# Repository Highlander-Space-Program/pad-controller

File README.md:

# Pad controller PCB

This PCB will be located on our static fire test stand. It will be responsibe for controlling the ignition and fuel systems.

Make sure to clone submodules when cloning this repository.

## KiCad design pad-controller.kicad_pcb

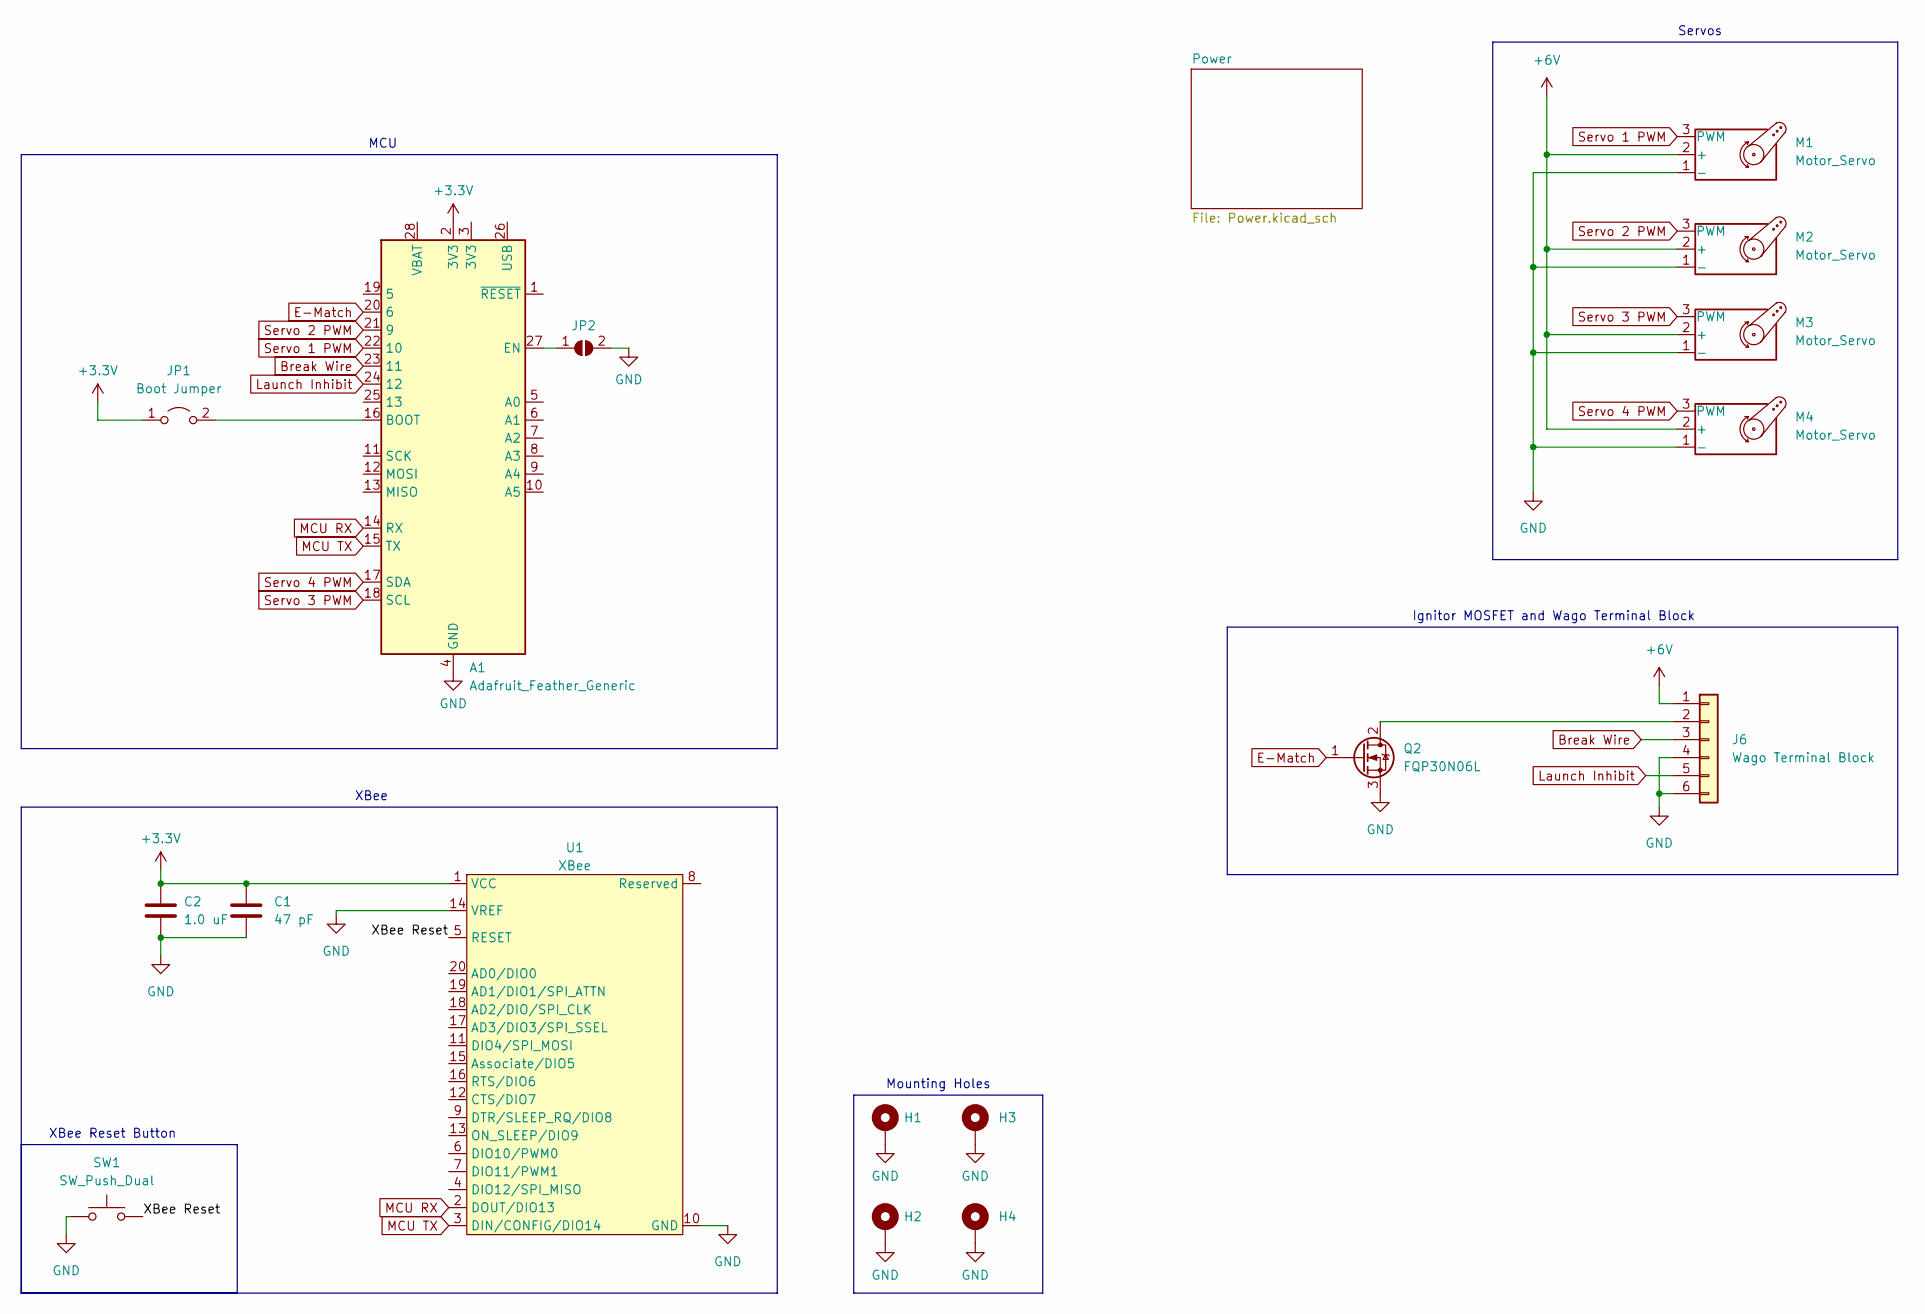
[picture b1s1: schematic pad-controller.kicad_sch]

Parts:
A1: Adafruit_Feather_Generic; Adafruit_Feather
C1: 47 pF; C_0805_2012Metric; Part No. GRM21A5C2D470JW01D
C2: 1.0 uF; C_0805_2012Metric; Part No. GRM219R7YA105MA12D
H1, H2, H3, H4: MountingHole_Pad; MountingHole_4mm_Pad_Via
J6: Wago Terminal Block; WAGO_2601-1106_lever_terminal_block; Part No. 2601-1106
JP1: Boot Jumper; PinHeader_1x02_P2.54mm_Vertical
JP2: SolderJumper-2_P1.3mm_Open_TrianglePad1.0x1.5mm
M1, M2, M3, M4: Motor_Servo; PinHeader_1x03_P2.54mm_Vertical
Q2: FQP30N06L; TO-220-3_Vertical; Part No. FQP30N06L
SW1: SW_Push_Dual; SW_PUSH_6mm
U1: XBee; XBee-PRO 900HP

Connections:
+3.3V: A1.2 (3V3), C1.1, C2.1, JP1.1 (A), U1.1 (VCC); also elsewhere on the board
+6V: J6.1, M1.2 (+), M2.2 (+), M3.2 (+), M4.2 (+); also elsewhere on the board
/XBee Reset: SW1.1, U1.5 (RESET)
Break Wire: A1.23 (11), J6.3
E-Match: A1.20 (6), Q2.1 (G)
GND: A1.4 (GND), C1.2, C2.2, H1.1, H2.1, H3.1, H4.1, J6.4, J6.6, JP2.2 (B), M1.1 (-), M2.1 (-), M3.1 (-), M4.1 (-), Q2.3 (S), SW1.2, U1.10 (GND), U1.14 (VREF); also elsewhere on the board
Launch Inhibit: A1.24 (12), J6.5
MCU RX: A1.14 (RX), U1.2 (DOUT/DIO13)
MCU TX: A1.15 (TX), U1.3 (DIN/CONFIG/DIO14)
unnamed: A1.27 (EN), JP2.1 (A)
unnamed: A1.16 (BOOT), JP1.2 (B)
unnamed: J6.2, Q2.2 (D)
Servo 1 PWM: A1.22 (10), M1.3 (PWM)
Servo 2 PWM: A1.21 (9), M2.3 (PWM)
Servo 3 PWM: A1.18 (SCL), M3.3 (PWM)
Servo 4 PWM: A1.17 (SDA), M4.3 (PWM)

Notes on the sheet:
Servos
Mounting Holes
XBee Reset Button
MCU
XBee
Ignitor MOSFET and Wago Terminal Block

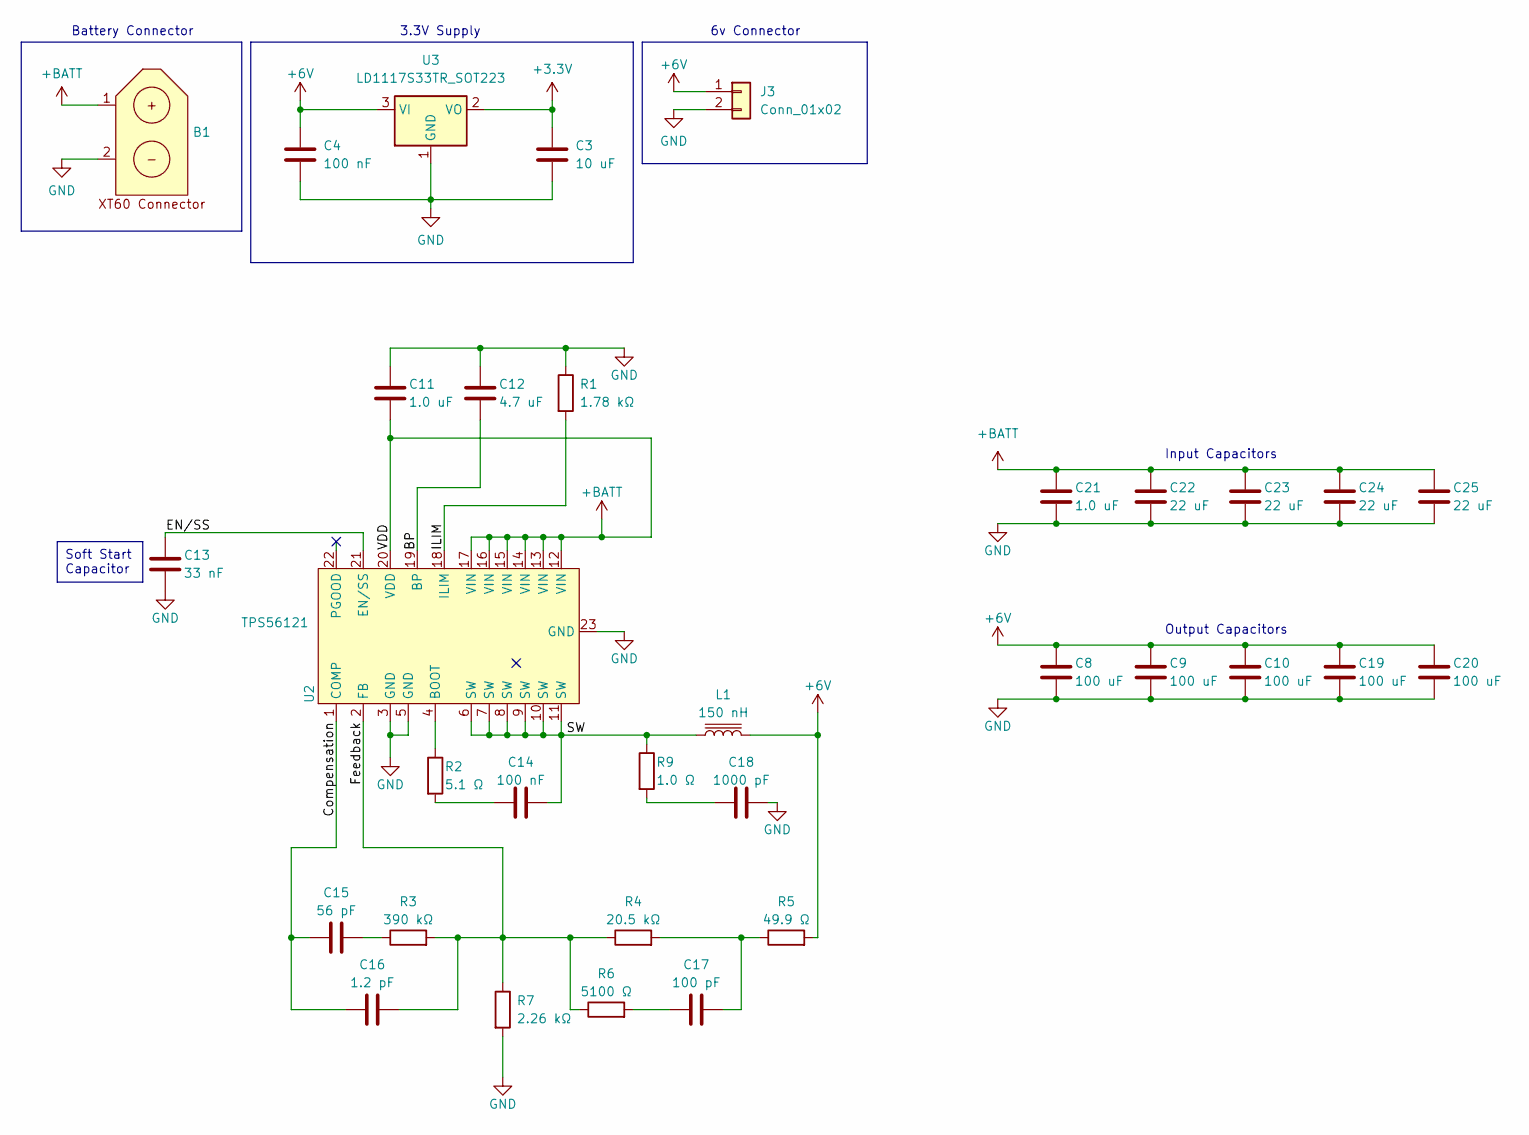
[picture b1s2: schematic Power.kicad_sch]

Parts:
B1: AMASS_XT60-M_1x02_P7.20mm_Vertical
C3: 10 uF; C_0805_2012Metric; Part No. GRM21BR61C106KE15K
C4, C14: 100 nF; C_0805_2012Metric; Part No. GCM21BR72A104KA37L
C8, C9, C10, C19, C20: 100 uF; C_1210_3225Metric; Part No. GRM32EC70J107ME15K
C11, C21: 1.0 uF; C_0805_2012Metric; Part No. GRM219R7YA105MA12D
C12: 4.7 uF; C_0805_2012Metric; Part No. GRM21BR71C475ME51K
C13: 33 nF; C_0805_2012Metric; Part No. GCM219R72A333KA37D
C15: 56 pF; C_0805_2012Metric; Part No. GRM21A5C2E560JW01D
C16: 1.2 pF; C_0805_2012Metric; Part No. CC0805BRNPO9BN1R2
C17: 100 pF; C_0805_2012Metric; Part No. CL21C101JCANNNC
C18: 1000 pF; C_0805_2012Metric; Part No. GRM2165C2A102JA01D
C22, C23, C24, C25: 22 uF; C_1210_3225Metric; Part No. GRM32ER71E226KE15K
J3: Conn_01x02; SolderWire-2sqmm_1x02_P7.8mm_D2mm_OD3.9mm
L1: 150 nH; L_Sumida_CDMC6D28_7.25x6.5mm; Part No. 0624CDMCCDS-R15MC
R1: 1.78 kΩ; R_0805_2012Metric; Part No. RC0805FR-071K78L
R2: 5.1 Ω; R_0805_2012Metric; Part No. RC0805FR-075R1L
R3: 390 kΩ; R_0805_2012Metric; Part No. RC0805FR-07390KL
R4: 20.5 kΩ; R_0805_2012Metric; Part No. RC0805FR-0720K5L
R5: 49.9 Ω; R_0805_2012Metric; Part No. RC0805FR-0749R9L
R6: 5100 Ω; R_0805_2012Metric; Part No. RC0805FR-075K1L
R7: 2.26 kΩ; R_0805_2012Metric; Part No. RC0805FR-072K26L
R9: 1.0 Ω; R_0805_2012Metric; Part No. RC0805FR-101RL
U2: TPS56121; DFN-22-1EP_5x6mm_P0.5mm_EP3.14x4.3mm
U3: LD1117S33TR_SOT223; SOT-223-3_TabPin2; Part No. LD1117S33TR

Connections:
+3.3V: C3.1, U3.2 (VO); also elsewhere on the board
+6V: C4.1, C8.1, C9.1, C10.1, C19.1, C20.1, L1.2, R5.2, U3.3 (VI); also elsewhere on the board
+BATT: B1.1, C11.2, C21.1, C22.1, C23.1, C24.1, C25.1, U2.12 (VIN), U2.13 (VIN), U2.14 (VIN), U2.15 (VIN), U2.16 (VIN), U2.17 (VIN), U2.20 (VDD)
/Power/BP: C12.2, U2.19 (BP)
/Power/Compensation: C15.2, C16.2, U2.1 (COMP)
/Power/EN/SS: C13.1, U2.21 (EN/SS)
/Power/Feedback: C16.1, R3.2, R4.1, R6.1, R7.1, U2.2 (FB)
/Power/ILIM: R1.2, U2.18 (ILIM)
/Power/SW: C14.2, L1.1, R9.1, U2.6 (SW), U2.7 (SW), U2.8 (SW), U2.9 (SW), U2.10 (SW), U2.11 (SW)
GND: B1.2, C3.2, C4.2, C8.2, C9.2, C10.2, C11.1, C12.1, C13.2, C18.1, C19.2, C20.2, C21.2, C22.2, C23.2, C24.2, C25.2, R1.1, R7.2, U2.3 (GND), U2.5 (GND), U2.23 (GND), U3.1 (GND); also elsewhere on the board
unnamed: C14.1, R2.2
unnamed: C15.1, R3.1
unnamed: C17.1, R4.2, R5.1
unnamed: C17.2, R6.2
unnamed: C18.2, R9.2
unnamed: R2.1, U2.4 (BOOT)

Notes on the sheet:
Soft Start Capacitor
Battery Connector
3.3V Supply
Input Capacitors
Output Capacitors
6v Connector

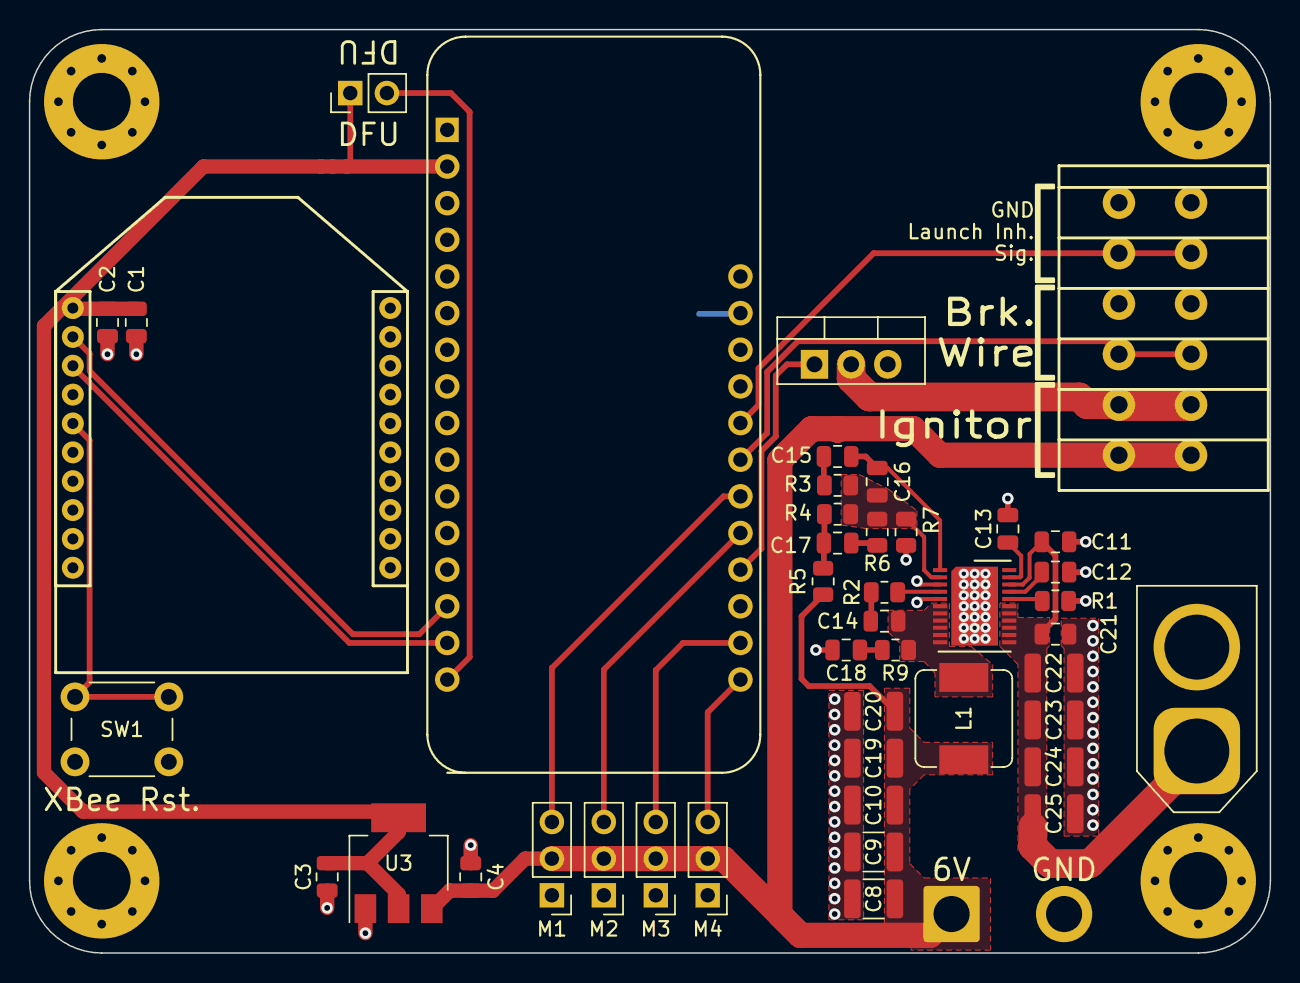
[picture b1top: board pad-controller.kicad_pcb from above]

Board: 2 copper layers, 86.0 x 64.0 mm, 50 parts (1 on the bottom side), 29 nets.

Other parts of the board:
J4: Conn_01x02; SolderWire-2sqmm_1x02_P7.8mm_D2mm_OD3.9mm

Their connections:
+6V: J4.1; also elsewhere on the board
GND: J4.2; also elsewhere on the board

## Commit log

2023-12-28 Copy design from Altium. Start selecting components for switching regulator.
2023-12-28 Add my symbol/footprint library as a git submodule
2023-12-28 Connect microcontroller to ingnitor mosfet and break wire connector
2023-12-28 Add XBee footprint
2023-12-29 Continue buck converter component selection
2023-12-30 Lay out the buck converter circuitry
2023-12-31 Lay out the rest of the components
2023-12-31 Add todo list to readme
2023-12-31 Replace ignitor mosfet with FQP30N06L
2023-12-31 Add part numbers for all capacitors
2024-01-01 Adjust layout
2024-01-01 Adjust buck converter thermal vias
2024-01-01 Filet board corners and extend ground plane to edge of board
2024-01-02 Add HSP logo and 3D model for wago terminal block
2024-01-03 Clean up schematic and board layout
2024-01-03 Update buck converter voltage divider values and part numbers
2024-01-03 Adjust back silkscreen
2024-01-03 Add silkscreen label for solder jumper
2024-01-05 Fix clearance issues between copper and board edge
2024-01-05 Reassign Feather pins to free up pin 13
